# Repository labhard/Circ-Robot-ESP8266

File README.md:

# Circ-Robot-ESP8266
Printed circit board to host a NodeMCU in a R/C mobile robot. The intended application is in MINI robot soccer of robocore.net events.
Ciruito impresso para suportar um NodeMCU para robô móvel de R/C. A aplicação de interesse é para equipar robôs em competições futebol categoria MINI dos eventos da Robocore.

Este projeto foi criado utilizando Kicad 8.
A fonte de alimentação recomendada: bateria de lítio 2S. Exemplo: duas células 18650 em série. Não há carregador embarcado.
O controle dos motores é feito com uma ponte H usando circuitos integrados como o MX1508 ou MX1616. Modelo de referência: https://www.robocore.net/driver-motor/mini-ponte-h-dupla-mx1616

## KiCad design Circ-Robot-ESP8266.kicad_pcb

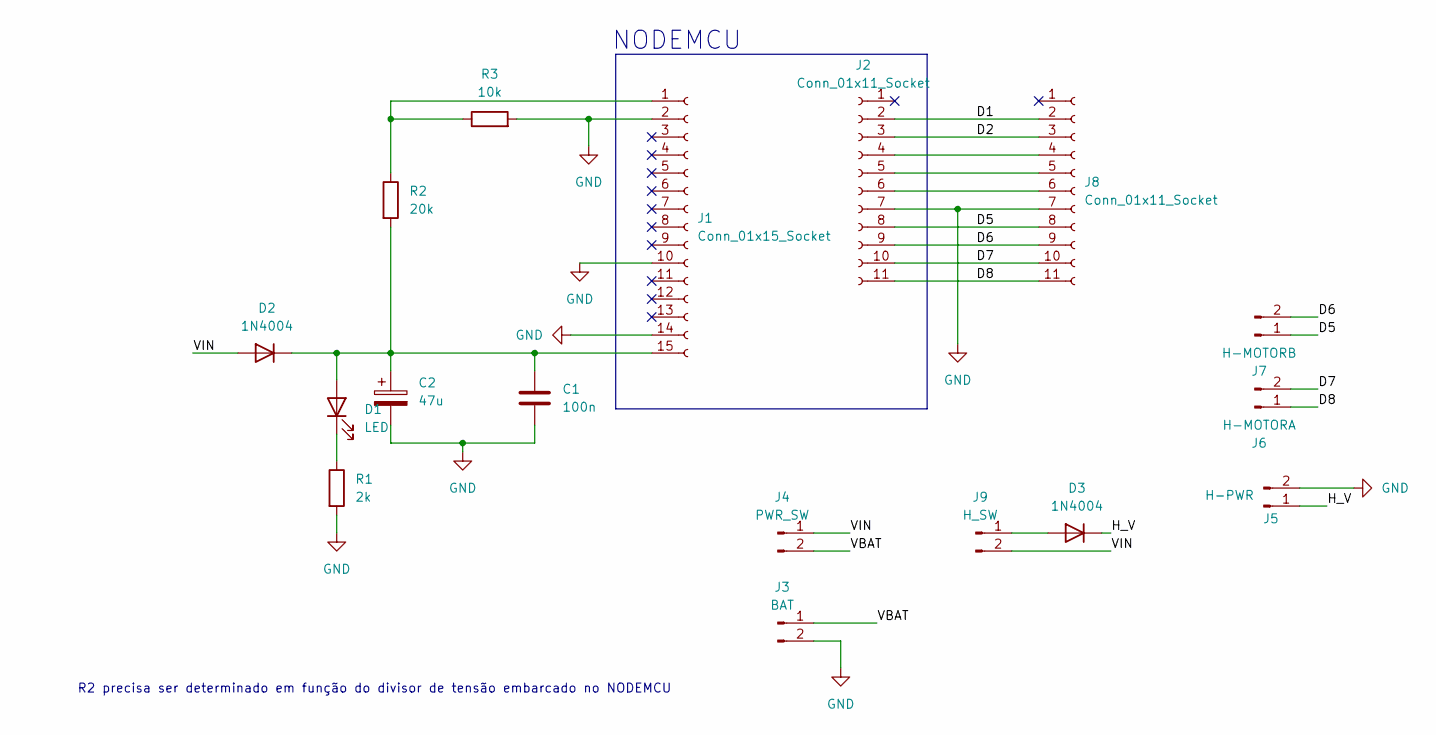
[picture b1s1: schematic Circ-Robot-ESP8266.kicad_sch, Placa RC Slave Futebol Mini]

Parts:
C1: 100n; CP_Radial_D5.0mm_P2.50mm
C2: 47u; CP_Radial_D5.0mm_P2.50mm
D1: LED; LED_D3.0mm
D2, D3: 1N4004; D_DO-41_SOD81_P10.16mm_Horizontal
J1: Conn_01x15_Socket; PinHeader_1x15_P2.54mm_Vertical
J2, J8: Conn_01x11_Socket; PinHeader_1x11_P2.54mm_Vertical
J3: BAT; PinHeader_1x02_P2.54mm_Vertical
J4: PWR_SW; PinHeader_1x02_P2.54mm_Vertical
J5: H-PWR; PinHeader_1x02_P2.54mm_Vertical
J6: H-MOTORA; PinHeader_1x02_P2.54mm_Vertical
J7: H-MOTORB; PinHeader_1x02_P2.54mm_Vertical
J9: H_SW; PinHeader_1x02_P2.54mm_Vertical
R1: 2k; R_Axial_DIN0207_L6.3mm_D2.5mm_P10.16mm_Horizontal
R2: 20k; R_Axial_DIN0207_L6.3mm_D2.5mm_P10.16mm_Horizontal
R3: 10k; R_Axial_DIN0207_L6.3mm_D2.5mm_P10.16mm_Horizontal

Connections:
/D1: J2.2, J8.2
/D2: J2.3, J8.3
/D5: J2.8, J7.1, J8.8
/D6: J2.9, J7.2, J8.9
/D7: J2.10, J6.2, J8.10
/D8: J2.11, J6.1, J8.11
/H_V: D3.1 (K), J5.1
/VBAT: J3.1, J4.2
/VIN: D2.2 (A), J4.1, J9.2
GND: C1.2, C2.2, J1.2, J1.10, J1.14, J2.7, J3.2, J5.2, J8.7, R1.2, R3.2
unnamed: C1.1, C2.1, D1.2 (A), D2.1 (K), J1.15, R2.2
unnamed: D1.1 (K), R1.1
unnamed: D3.2 (A), J9.1
unnamed: J1.1, R2.1, R3.1
unnamed: J2.4, J8.4
unnamed: J2.5, J8.5
unnamed: J2.6, J8.6

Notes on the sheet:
R2 precisa ser determinado em função do divisor de tensão embarcado no NODEMCU
NODEMCU

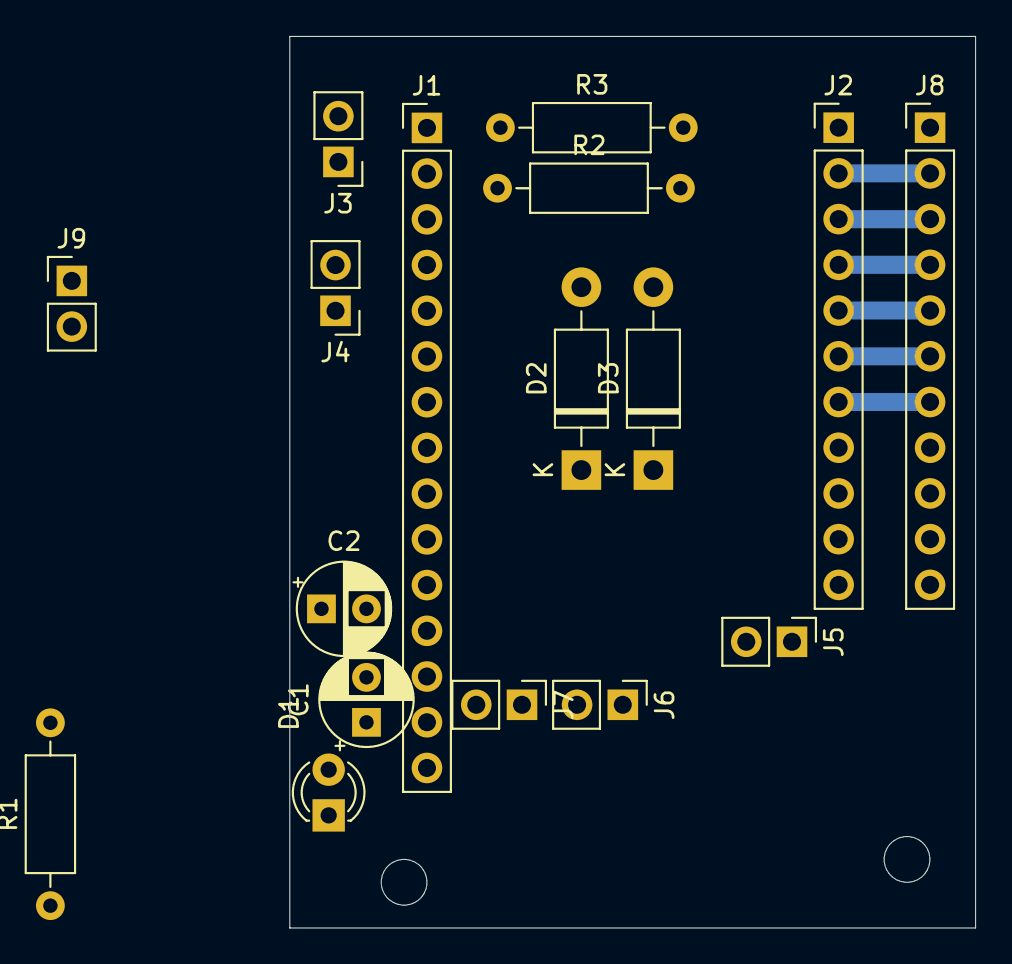
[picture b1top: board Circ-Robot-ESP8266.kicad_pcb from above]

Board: 2 copper layers, 38.1 x 49.5 mm, 17 parts (0 on the bottom side), 17 nets.

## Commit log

2026-01-30 Adicionando o projeto Kicad pela primeira vez
